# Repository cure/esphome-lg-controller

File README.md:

# ESPHome LG AC Wired Controller
Wired controller for LG Air Conditioners using an ESP32 microcontroller and [ESPHome](https://esphome.io/). It can be used to control an indoor unit from [Home Assistant](https://www.home-assistant.io/).

This has some advantages compared to the [LG ThinQ integration](https://github.com/ollo69/ha-smartthinq-sensors):
* Can override the unit's room temperature thermistor with a Home Assistant temperature sensor.
* Does not depend on LG's ThinQ cloud service.
* Supports units without a Wifi module.
* No annoying sounds from the AC unit when changing settings through the controller.
* More settings and information available (although some settings like display light on/off are available in ThinQ but aren't passed to the wired controller).

# Compatibility
### Supported AC units
If your indoor unit supports the LG PREMTB100 and/or LG PREMTA200 controller, it will very likely be compatible.

The [wiki](https://github.com/JanM321/esphome-lg-controller/wiki) has a list of LG AC units that have been tested with this controller.

### Multiple controllers
It's possible to connect multiple controllers to a single indoor unit, but one of them must be set as 'master' and the others as 'slave'. Since February 2024, this ESPHome controller has experimental support for this. I'm not using this myself, so there might be some issues with this (please report them).

The room temperature sensor is ignored for 'slave' controllers, so if you want to use this controller with an LG controller and use a Home Assistant temperature sensor, the LG controller must be set as 'slave'.

### Details
There seem to be two different protocols that LG AC units and wall controllers use to communicate: 
1. **6-byte protocol**: the controller sends a 6-byte message every four seconds or so and the AC unit responds with a 6-byte message. This is the more basic protocol and likely older because it doesn't support advanced features and settings. An ESPHome implementation of this is available here: https://github.com/Flameeyes/esphome-lg-pqrcuds0
2. **13-byte [protocol](protocol.md)**: the controller sends a 13-byte status message every 20 seconds (or when there's a change in settings) and the AC unit sends a very similar status message every 60 seconds. There are also other message types for more advanced settings. **This is the one implemented here.**

The controller hardware is identical because both use a very slow serial connection (104 bps) over a three-wire cable (Red = 12V, Yellow = Signal, Black = GND). In fact, some LG controllers support both protocols: my LG PREMTB001 controller first tries the 13-byte protocol and if it doesn't receive a response it will switch to the 6-byte protocol. My LG PREMTB100 (newer controller) only supports the 13-byte protocol as far as I can tell.

Wired controllers must be connected to the CN-REMO socket on the indoor unit's PCB (green 3 pin JST-XH connector). Fortunately my wall units came with a short extension cable already plugged into that port so I only had to open up the bottom part of the unit to connect my controller.

Wired controllers using the new protocol only send and receive settings and current temperature. The HVAC unit itself decides when to start/stop active cooling/heating etc based on this. It's possible to use a Home Assistant template sensor as temperature sensor to influence this behavior (see below).

See [protocol.md](protocol.md) for information about the protocol based on reverse engineering the PREMTB001 and PREMTB100 controllers.

# Hardware
There are three different PCB designs. The "hardware-tiny" variant is most popular at this point. The "hardware-FeatherS3" PCB is a more recent addition.

## "hardware" (original, June 2023)

You need at least the following parts for each indoor unit:
* PCB. See the original PCB in the [hardware/](hardware/) directory
* ESP32 DevKitC board. I used an Espressif ESP32-DevKitC-32E.
* Cable with JST-XH connector to connect the PCB to the AC. I used an Adafruit 4873 cable.

The `hardware/` PCB I ordered from [PCBWay](https://www.pcbway.com/QuickOrderOnline.aspx).

## "hardware-tiny" (November 2023)

You need at least the following parts for each indoor unit:
* PCB. See the cheaper and smaller PCB in the [hardware-tiny/](hardware-tiny/) directory.
* ESP32 DevKitC board. I used an Espressif ESP32-DevKitC-32E.
* Cable with JST-XH connector to connect the PCB to the AC. I used an Adafruit 4873 cable.

The `hardware-tiny/` PCB can be ordered from [JLCPCB](https://cart.jlcpcb.com/quote/) (see instructions [here](https://github.com/JanM321/esphome-lg-controller/issues/2#issuecomment-1801803656)).

## "hardware-FeatherS3" (May 2025)

You need at least the following parts for each indoor unit:
* PCB. See the even smaller PCB in the [hardware-FeatherS3/](hardware-FeatherS3/) directory.
* Unexpected Maker's [ESP32 FeatherS3](https://esp32s3.com/feathers3.html)
* Cable with JST-XH connector to connect the PCB to the AC. I used an Adafruit 4873 cable.

This PCB supports the more modern [FeatherS3 by Unexpected Maker](https://esp32s3.com/feathers3.html), which has a USB-C connector. The FeatherS3 [can be powered from the 3.3V pin](https://help.unexpectedmaker.com/index.php/knowledge-base/can-i-power-my-board-from-the-3v3-pin/), which is what is assumed here. The USB-C connector should not be connected at the same time; if you want to power the FeatherS3 via USB, you should not connect the 3.3V pin.

The `hardware-FeatherS3/` PCB can be ordered from [JLCPCB](https://cart.jlcpcb.com/quote/).

JLCPCB ordering instructions:

* Upload [`GERBER-lg_hvac_esp32.zip`](hardware-FeatherS3/jlcpcb/production_files/GERBER-lg_hvac_esp32.zip) as the gerber file, leave all settings default.
* Enable the `Assembly` option at the bottom of the quote page and proceed.
* Upload [`BOM-lg_hvac_esp32.csv`](hardware-FeatherS3/jlcpcb/production_files/BOM-lg_hvac_esp32.csv) for the bom file and [`CPL-lg_hvac_esp32.csv`](hardware-FeatherS3/jlcpcb/production_files/CPL-lg_hvac_esp32.csv) for placement / cpl

I paid about $50 for five boards, fully assembled, before any shipping and import duties.

*Note: if you use the FeatherS3 PCB, you'll also need to make some changes to `esphome/base.yaml` for ESPHome as part of the next step. See the FeatherS3 comments in that file.*

# ESPHome Firmware
I used the following steps to build the ESPHome firmware, flash it on the device, and add the controller in Home Assistant:
1. Clone this repository and navigate to the `esphome` directory.
2. Install ESPHome command line tools on Linux: https://esphome.io/guides/installing_esphome.html
3. Ensure the Python virtual environment is activated (`source venv/bin/activate`).
4. Copy `template.yaml` to (for example) `lg-livingroom.yaml` and edit the lines marked with `XXX`.
5. Connect the ESP32 DevKitC board to your computer with a micro USB cable. This is only needed the first time, after that it can use OTA updates over wifi.
6. Run `esphome run lg-livingroom.yaml` to build the firmware and upload it to the device.
7. The device can now be added in Home Assistant (Settings => Devices & Services). HA will ask you for the encryption key from the YAML file.
8. Disconnect the micro USB cable.
9. Install the ESP32 DevKitC board on the PCB and connect the PCB to the AC.

If you just want to connect to the device to view the debug logs, use `esphome logs lg-livingroom.yaml`.

# Features
Features currently available in Home Assistant:
* Operation mode (off, auto, cool, heat, dry/dehumidify, fan only).
* Target temperature (0.5°C steps).
* Use of a Home Assistant temperature sensor for room temperature (rounded to nearest 0.5°C). 
* Fan speed (slow, low, medium, high, auto).
* Swing mode (off, vertical, horizontal, both).
* Airflow up/down setting from 0-6 for up to 4 vanes (vane angle, with 0 being default for operation mode).
* Switch for external vs internal thermistor.
* Switch for air purifier (plasma) on/off.
* Switch and binary sensor for Auto Dry (also known as Auto Clean) feature. Used to dry indoor unit when it's turned off after cooling/dehumidifying.
* Sensors for reporting outdoor unit on/off, defrost, preheat, error code.
* Sensors for reporting in/mid/out pipe temperatures (if supported by unit).
* Input field for sleep timer from 0 to 420 minutes (0 turns off the sleep timer).
* Input fields for fan speed installer setting (to fine-tune fan speeds, 0-255 with 0 being factory default). This is installer setting 3 (ESP Setting) on LG controllers.
* Select option for over heating installer setting from 0-4 (to change over heating behavior in heating mode). This is installer setting 15 (Over Heating) on LG controllers.
* YAML options for Fahrenheit mode and 'slave' controller mode.
* Detects & exposes only supported operation/fan/swing modes for the connected indoor unit.

The LG ThinQ app and wireless remote can still be used to change these settings and other settings. They'll be synchronized with this controller.

Unfortunately not all settings are exposed to the wired controller, but if you're interested in a feature and it's supported by the PREMTB100 or PREMTA200 controller, please open an issue and we can consider adding it.

# Tips
* [Issue #43](https://github.com/JanM321/esphome-lg-controller/issues/43) has some information on temperature sensors that work well for this.
* It's possible to use a Home Assistant template sensor as room temperature sensor. I'm [using this](https://gist.github.com/JanM321/b550285713f20231386509b2c227f0b8) to work around some issues with my LG Multi F unit in heating mode.

# PCB (details)
***❗ Update November 2023: This section is for my original PCB in the hardware/ directory. [Florian Brede](https://github.com/florianbrede-ayet) has designed a smaller and cheaper PCB that can be ordered from JLCPCB. It's in the [hardware-tiny/](hardware-tiny/) directory.***

See [hardware/](hardware/) for schematic and list of materials. This part was based on the excellent work and research by [@Flameeyes](https://github.com/Flameeyes):
* https://flameeyes.blog/tag/lg/
* https://github.com/Flameeyes/esphome-lg-pqrcuds0

The hardware needs four main components:
1) **Microcontroller**. Similar to their setup, I used an Espressif ESP32-DevKitC-32E board (it has the ESP32-WROOM-32E module).
A devkit module is nice for this because it doesn't need any external components. My PCB has two female pin headers connecting it to the board. This also makes it easy to replace or upgrade if needed.
2) **Transceiver**. This is needed because the AC has a single (12V) signal wire but the microcontroller has separate (lower-voltage) RX/TX pins. I used a [TI TLIN1027DRQ1](https://www.ti.com/product/TLIN1027-Q1/part-details/TLIN1027DRQ1) LIN transceiver. LIN transceivers are typically used in the automotive industry but work well for this too. As [explained](https://flameeyes.blog/2021/06/29/lg-aircon-reversing-part-2-buses-and-cars/) by Flameeyes, it's important to use a LIN transceiver without the "TXD-Dominant Timeout" feature because LG's very slow ~104 bps serial connection can trigger that timeout and this will corrupt the signal.
3) **Voltage regulator**. This is needed because the AC supplies 12V but the microcontroller requires 3.3V. I replaced the voltage regulator part with a [Traco Power TSRN 1-2433](https://www.tracopower.com/int/model/tsrn-1-2433) step-down switching regulator because it doesn't require any external components such as capacitors or inductors. (In hindsight, the [Traco Power TSR 1-2433](https://www.tracopower.com/int/model/tsr-1-2433) might have been better because it's cheaper and has better availability.)
4) **Connector**. To connect the PCB to the AC. I used a screw terminal for this.

My PCB also has some capacitors, resistors and diodes that are based on the TLIN1027DRQ1 data sheet. I'm not sure if these are really necessary but I included them to be safe and it works well. I used SMT components if available because I had the PCBs assembled by [PCBWay](https://www.pcbway.com/). **Update november 2023: the hardware-tiny/ PCB can be ordered from JLCPCB.**

Note: an alternative for the LIN transceiver is the opto-isolator design used here:
* https://github.com/AussieMakerGeek/LG_Aircon_MQTT_interface
* https://www.instructables.com/Hacking-an-LG-Ducted-Split-for-Home-Automation/

# License
This project is licensed under the 0BSD License. See the LICENSE file for details.
This basically means you can use it however you want. Attribution is not required but would be greatly appreciated.

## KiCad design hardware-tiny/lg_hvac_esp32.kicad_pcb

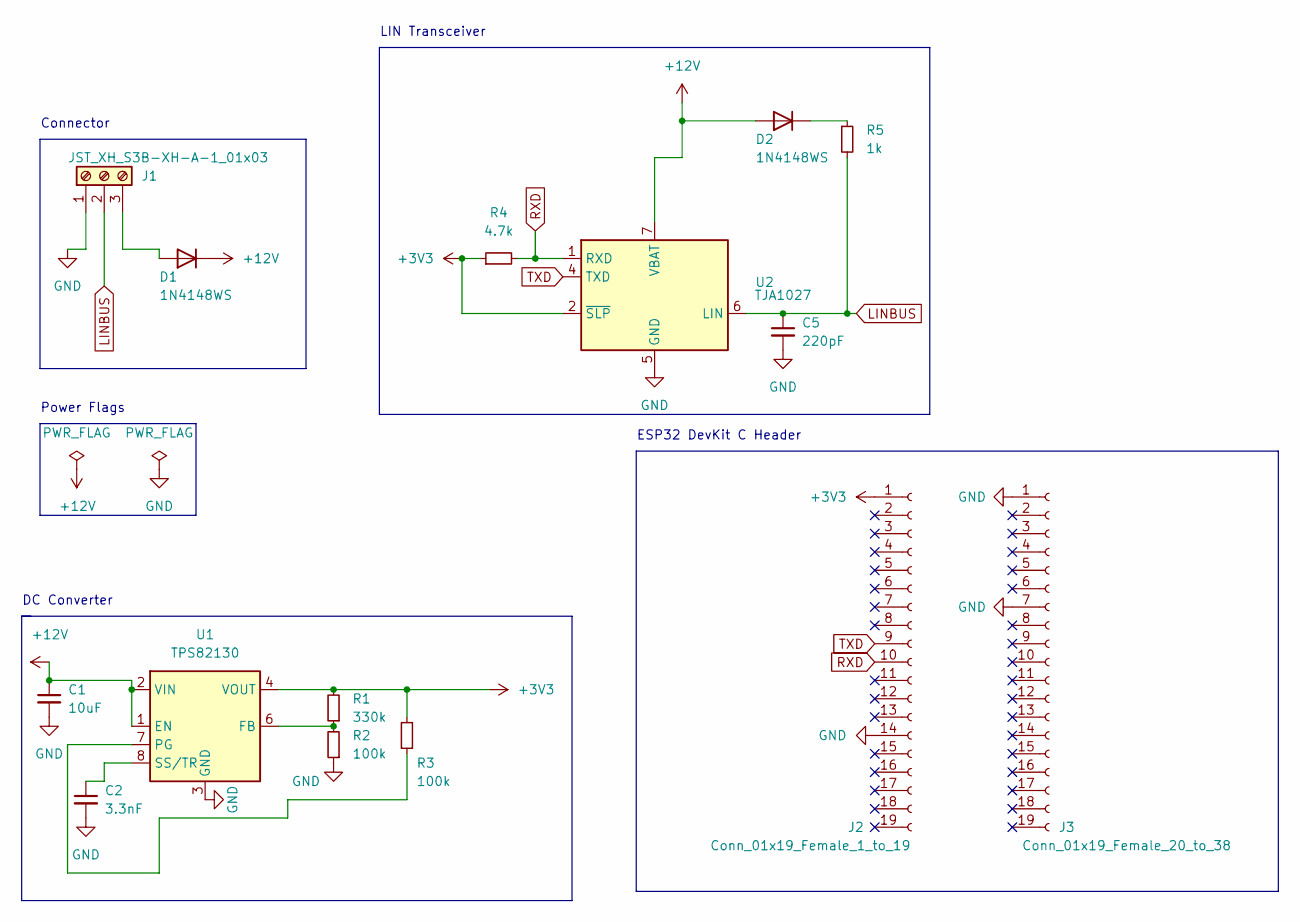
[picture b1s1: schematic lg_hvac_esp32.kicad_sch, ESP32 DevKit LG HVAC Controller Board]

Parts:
C1: 10uF; C_1210_3225Metric; LCSC C92834
C2: 3.3nF; C_0402_1005Metric; LCSC C26404
C5: 220pF; C_0402_1005Metric; LCSC C343058
D1, D2: 1N4148WS; D_SOD-323; LCSC C727111
J1: JST_XH_S3B-XH-A-1_01x03; JST_XH_S3B-XH-A-1_1x03_P2.50mm_Horizontal; LCSC C157928
J2: Conn_01x19_Female_1_to_19; PinSocket_1x19_P2.54mm_Vertical; LCSC C2932678
J3: Conn_01x19_Female_20_to_38; PinSocket_1x19_P2.54mm_Vertical; LCSC C2932678
R1: 330k; R_0805_2012Metric; LCSC C17629
R2, R3: 100k; R_0805_2012Metric; LCSC C149504
R4: 4.7k; R_0805_2012Metric; LCSC C17673
R5: 1k; R_0805_2012Metric; LCSC C17513
U1: TPS82130; Texas_SIL0008D_MicroSiP-8-1EP_2.8x3mm_P0.65mm_EP1.1x1.9mm_T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; LCSC C473914
U2: TJA1027; SOIC-8_3.9x4.9mm_P1.27mm; LCSC C194371

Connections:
+3V3: J2.1, R1.2, R3.2, R4.1, U1.4 (VOUT), U1.5 (VOUT), U2.2 (~SLP)
+12V: C1.1, D1.1 (K), D2.2 (A), U1.1 (EN), U1.2 (VIN), U2.7 (VBAT)
GND: C1.2, C2.2, C5.2, J1.1, J2.14, J3.1, J3.7, R2.1, U1.3 (GND), U1.9 (GND), U2.5 (GND)
LINBUS: C5.1, J1.2, R5.2, U2.6 (LIN)
unnamed: D1.2 (A), J1.3
unnamed: D2.1 (K), R5.1
unnamed: R1.1, R2.2, U1.6 (FB)
unnamed: R3.1, U1.7 (PG)
unnamed: C2.1, U1.8 (SS/TR)
RXD: J2.10, R4.2, U2.1 (RXD)
TXD: J2.9, U2.4 (TXD)

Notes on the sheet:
DC Converter
Connector
LIN Transceiver
Power Flags
ESP32 DevKit C Header

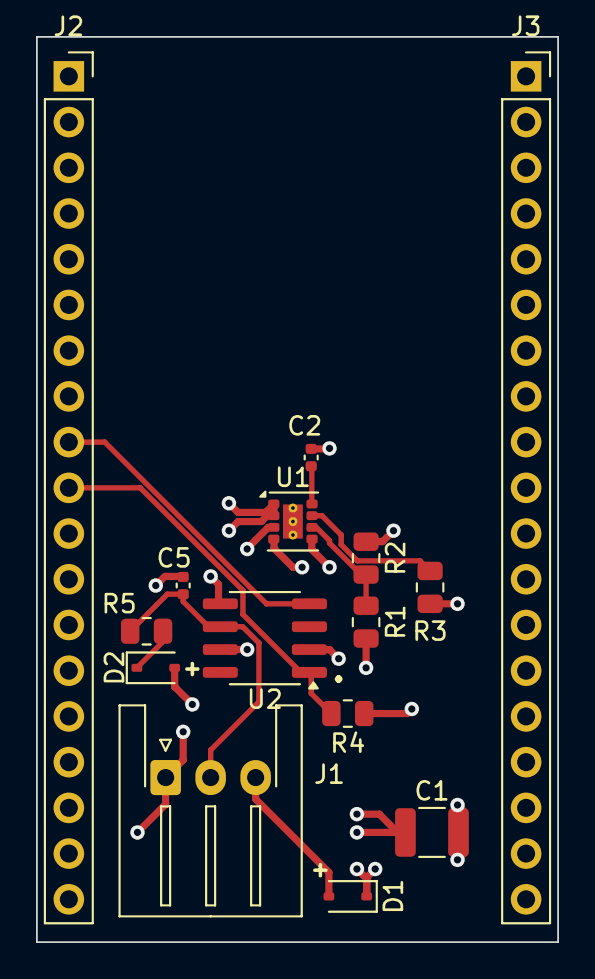
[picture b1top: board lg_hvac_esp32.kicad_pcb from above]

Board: 4 copper layers, 29.0 x 50.3 mm, 15 parts (0 on the bottom side), 11 nets.

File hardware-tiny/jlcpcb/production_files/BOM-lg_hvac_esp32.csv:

Comment,Designator,Footprint,LCSC,Quantity
100k,"R2,R3",R_0805_2012Metric,C149504,2
JST_XH_S3B-XH-A-1_01x03,J1,JST_XH_S3B-XH-A-1_1x03_P2.50mm_Horizontal,C157928,1
1k,R5,R_0805_2012Metric,C17513,1
330k,R1,R_0805_2012Metric,C17629,1
4.7k,R4,R_0805_2012Metric,C17673,1
TJA1027,U2,SOIC-8_3.9x4.9mm_P1.27mm,C194371,1
3.3nF,C2,C_0402_1005Metric,C26404,1
Conn_01x19_Female_1_to_19,"J2,J3",PinSocket_1x19_P2.54mm_Vertical,C2932678,2
220pF,C5,C_0402_1005Metric,C343058,1
TPS82130,U1,Texas_SIL0008D_MicroSiP-8-1EP_2.8x3mm_P0.65mm_EP1.1x1.9mm_ThermalVias,C473914,1
1N4148WS,"D1,D2",D_SOD-323,C727111,2
10uF,C1,C_1210_3225Metric,C92834,1

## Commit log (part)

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2025-05-04 Replaced C1 with a component that is available at jlcpcb.
    Fixed all DRC errors and warnings.
    Updated project files for KiCAD 9. I used the
    https://github.com/Bouni/kicad-jlcpcb-tools plugin with some custom
    rotation settings for J1, J2, and J3 because the KiCAD library and
    jlcpcb disagree.
2026-05-23 Stop using deprecated EntityBase::set_internal methods (fixes #158)
